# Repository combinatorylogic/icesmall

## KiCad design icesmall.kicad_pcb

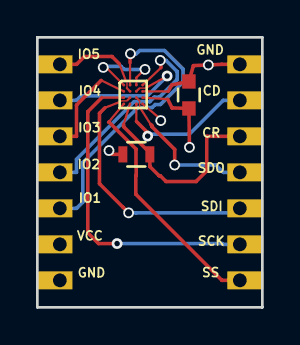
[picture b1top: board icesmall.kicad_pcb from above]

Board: 4 copper layers, 12.5 x 15.0 mm, 5 parts (0 on the bottom side), 13 nets.

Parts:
C1: 0.1u; C_0603
P1, P2: CONN_01X07; HPADS7
R1: 10k; R_0603
U2: iCE40-LP1K-SWG16; WLCS16

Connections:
+3V3: C1.2, P1.2, R1.2, U2.A1, U2.A3, U2.C4
FPGA_CDONE: P2.2, U2.D3
FPGA_CRESETB: P2.3, R1.1, U2.D2
FPGA_SCK: P2.6, U2.C1
FPGA_SDI: P2.5, U2.C2
FPGA_SDO: P2.4, U2.C3
FPGA_SS: P2.7, U2.D1
GND: C1.1, P1.1, P2.1, U2.B4, U2.D4
IO1: P1.3, U2.A2
IO2: P1.4, U2.A4
IO3: P1.5, U2.B1
IO4: P1.6, U2.B3
IO5: P1.7, U2.B2

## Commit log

2018-04-29 Moving to git: a small breakout board for ice40lp1k WLCS-16
2018-04-29 Add a submodule
